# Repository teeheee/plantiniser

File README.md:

# Description

A watering system

# Usage Guide

# Platformio Commands

## Run unit tests

> pio test -e native

## Run hardware interface tests

> pio run -e hal_test -t upload

## RUN main program

> pio run -e main -t upload

## interface over usb

> pio run -e main -t monitor

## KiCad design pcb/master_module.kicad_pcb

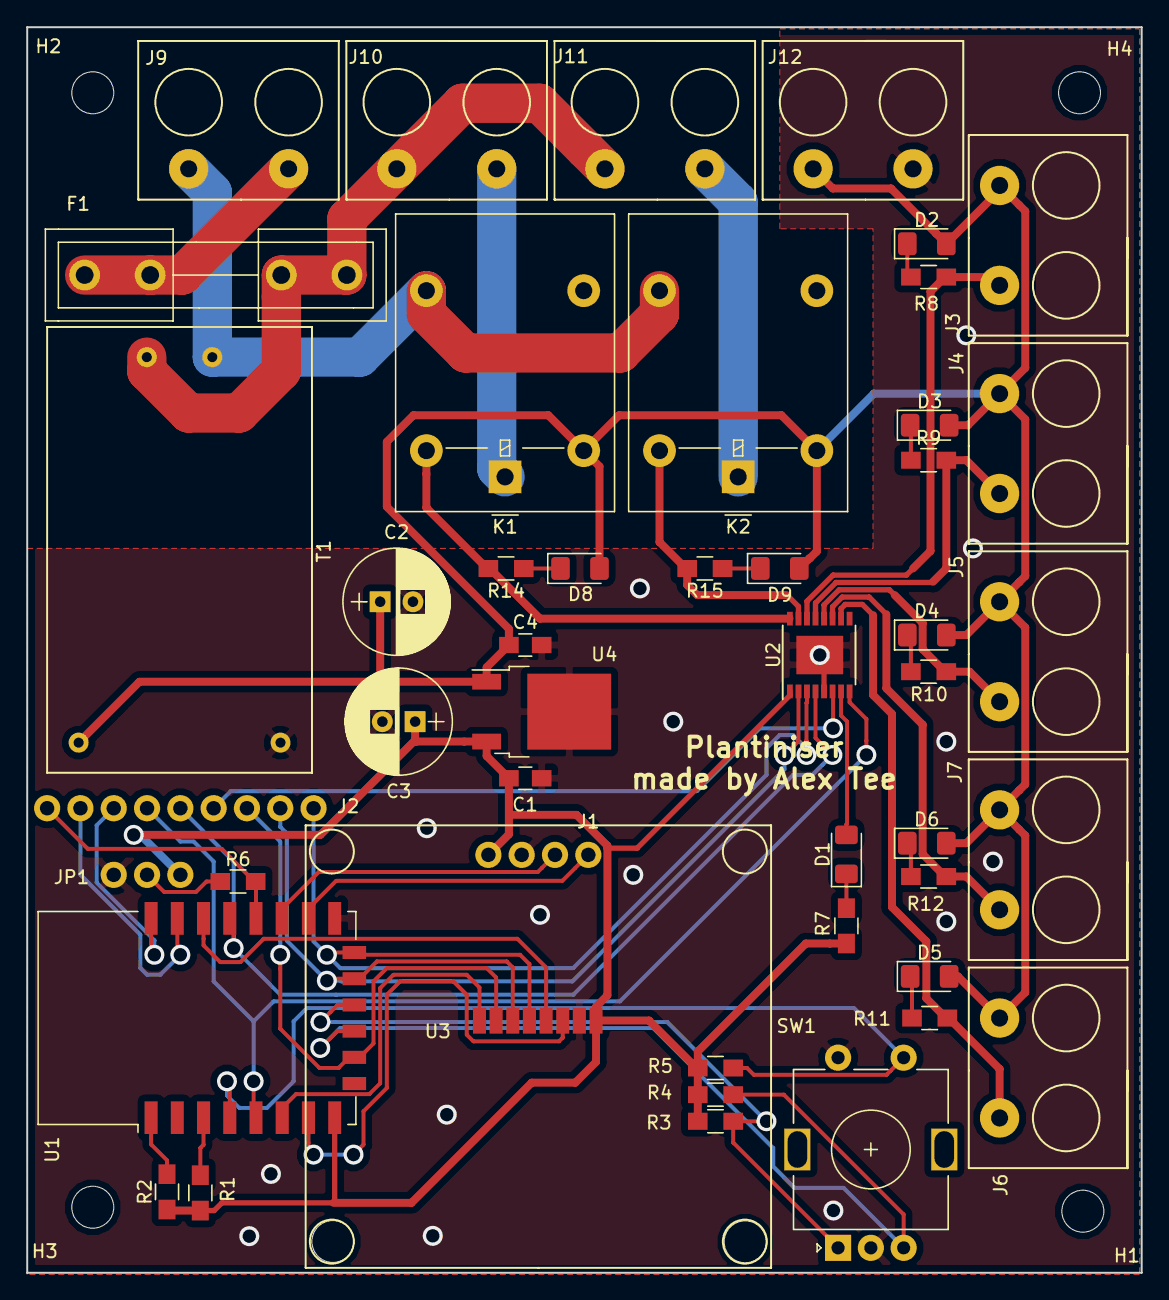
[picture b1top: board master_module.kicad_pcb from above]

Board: 2 copper layers, 85.0 x 95.0 mm, 51 parts (0 on the bottom side), 44 nets.

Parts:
C1, C4: 100nF; Kondensator_SMD_0805
C2, C3: 47uF; Kondensator_THT_8mm
D1, D2, D3, D4, D5, D6, D8, D9: LED; LED_SMD_1206
F1: Fuse; Sicherung_THT
H1, H2, H3, H4: MountingHole; MountingHole_3.2mm_M3_DIN965
J1: OLED; i2c_oled_1.3Zoll
J2: interface; CON_Stiftleiste_9x1
J3: 12V_OUT1; terminal_block_2pin
J4: 12V_OUT2; terminal_block_2pin
J5: 12V_OUT3; terminal_block_2pin
J6: 12V_OUT4; terminal_block_2pin
J7: 12V_OUT5; terminal_block_2pin
J9: 230V; terminal_block_2pin
J10: 230V_OUT1; terminal_block_2pin
J11: 230V_OUT2; terminal_block_2pin
J12: 12V_IN; terminal_block_2pin
JP1: Flash; CON_Stiftleiste_3x1
K1, K2: FINDER-40.11; Relay_SPDT_Omron-G5LE-1
R1, R2, R3, R4, R5, R6, R7: R; Wiederstand_SMD_0805
R8, R9, R10, R11, R12, R14, R15: 300; Wiederstand_SMD_0805
SW1: Rotary_Encoder_Switch; RotaryEncoder_Alps_EC11E-Switch_Vertical_H20mm
T1: HLK-PM12
U1: ESP-12E
U2: DRV8860_PWPR; TSSOP-16-1EP_4.4x5mm_P0.65mm
U3: NRF24L01; NRF24L01-SMD
U4: LF33_TO252; TO-252-2

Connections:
+3V3: C1.1, C3.1, J1.4, JP1.1, R1.1, R2.1, R3.1, R4.1, R5.1, R7.2, U1.8, U2.1, U3.2, U4.3
+12V: C2.1, C4.1, D2.2, D3.2, D4.2, D5.2, D6.2, D8.2, D9.2, J3.1, J4.1, J5.1, J6.1, J7.1, J12.1, K1.2, K2.2, T1.4, U4.1
/230V_A: F1.2, J9.2
/230V_B: F1.1, J10.1, J11.1, T1.2
/230V_C: J9.1, K1.4, K2.4, T1.1
/230V_E: J10.2, K1.1
/230V_F: J11.2, K2.1
/MISO: J2.7, U1.10, U3.7
/MOSI: J2.8, U1.13, U2.2, U3.6
/RE3: J3.2, R8.2, U2.14
/RE4: J4.2, R9.2, U2.13
/RE5: J5.2, R10.2, U2.12
/RE6: J7.2, R12.2, U2.11
/RE7: J6.2, R11.2, U2.10
/SCLK: J2.9, U1.14, U2.3, U3.5
A: R3.2, SW1.A, U1.12
B: R4.2, SW1.B, U1.11
C: R5.2, SW1.S1, U1.4
CE: U1.7, U3.3
CSN: U1.20, U3.4
DOUT: J2.6, U2.6
ENABLE: J2.4, U1.5, U2.8
GND: C1.2, C2.2, C3.2, C4.2, J1.3, J12.2, JP1.3, SW1.C, SW1.S2, T1.3, U1.15, U2.5, U2.17, U3.1, U4.2
GPIO0: J2.1, R6.2, U1.18
IRQ: U1.6, U3.8
LATCH: J2.5, U1.19, U2.4
unnamed: D1.1, R7.1
unnamed: D1.2, U2.7
unnamed: D2.1, R8.1
unnamed: D3.1, R9.1
unnamed: D4.1, R10.1
unnamed: D5.1, R11.1
unnamed: D6.1, R12.1
unnamed: D8.1, R14.1
unnamed: D9.1, R15.1
unnamed: JP1.2, R6.1
unnamed: R1.2, U1.3
unnamed: R2.2, U1.1
RE1: K1.5, R14.2, U2.16
RE2: K2.5, R15.2, U2.15
RX: J2.2, U1.21
SCL: J1.2, U1.17
SDA: J1.1, U1.16
TX: J2.3, U1.22

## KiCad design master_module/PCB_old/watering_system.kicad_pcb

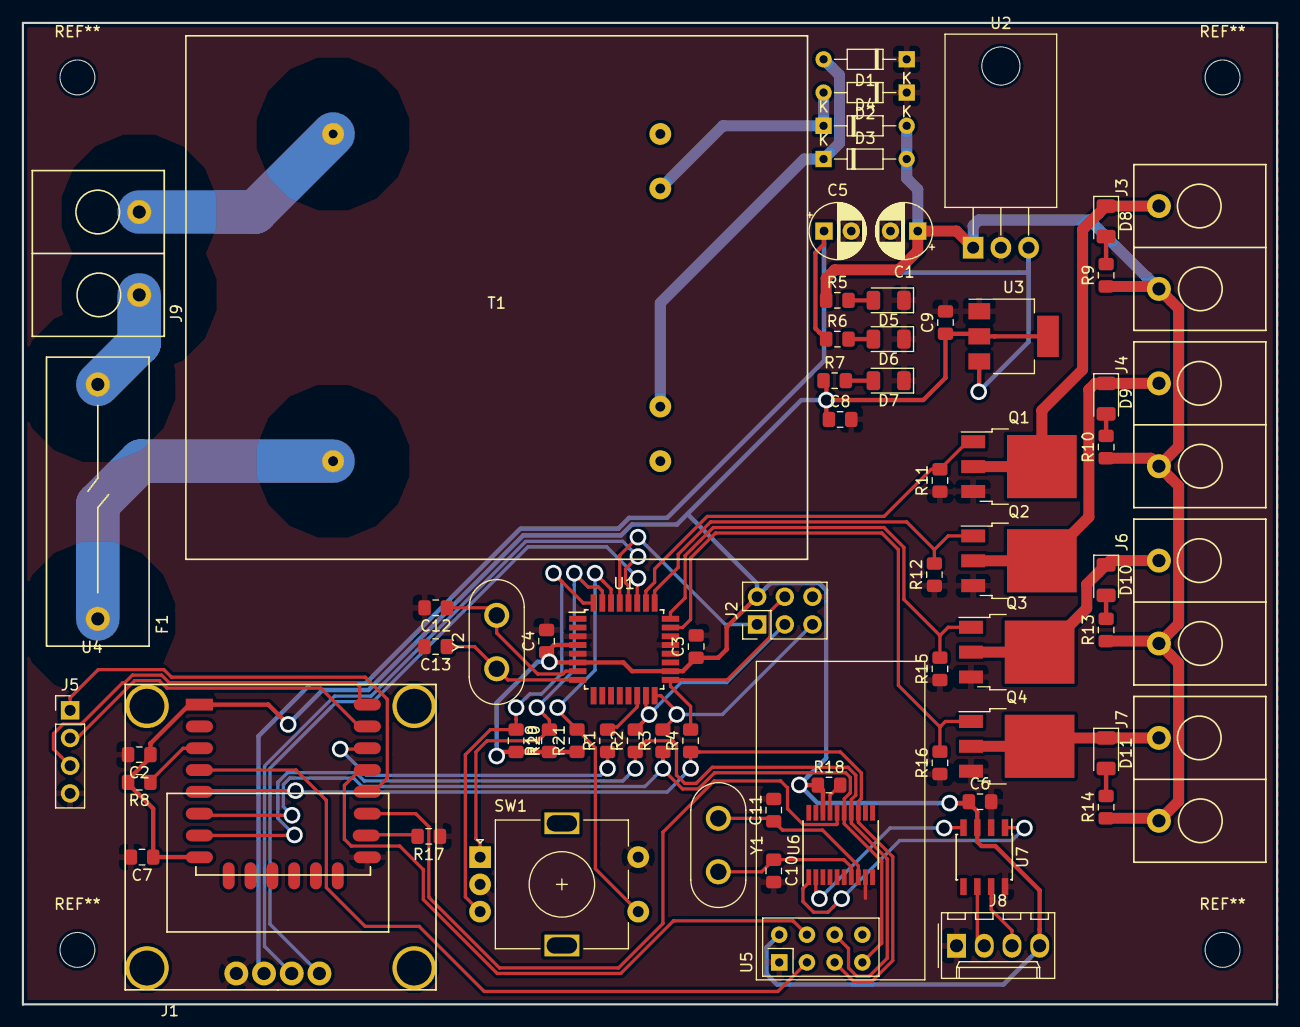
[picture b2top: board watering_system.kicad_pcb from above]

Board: 2 copper layers, 115.0 x 90.0 mm, 70 parts (0 on the bottom side), 55 nets.

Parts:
C1, C5: 47u; CP_Radial_D5.0mm_P2.50mm
C2, C3, C4, C6, C7, C8, C9: 100n; C_0805_2012Metric_Pad1.15x1.40mm_HandSolder
C10, C11, C12, C13: 22p; C_0805_2012Metric_Pad1.15x1.40mm_HandSolder
D1, D2, D3, D4: DIODE; D_DO-34_SOD68_P7.62mm_Horizontal
D5, D6, D7, D8, D9, D10, D11: LED; LED_1206_3216Metric
F1: Fuse; fuse
J1: Oled; i2c_oled_0_95_inch
J2: AVR-ISP-6; PinHeader_2x03_P2.54mm_Vertical
J3: A1_CON; HP_Connector_2pin
J4: A2_CON; HP_Connector_2pin
J5: esp_serial; PinHeader_1x04_P2.54mm_Vertical
J6: A3_CON; HP_Connector_2pin
J7: A4_CON; HP_Connector_2pin
J8: CAN; Molex_KK-254_AE-6410-04A_1x04_P2.54mm_Vertical
J9: MAINS; HP_Connector_2pin
Q1, Q2, Q3, Q4: IRFR1205; TO-252-3_TabPin2
R1, R2, R3, R4, R5, R8, R9, R10, R11, R12, R13, R14, R15, R16, R17, R18, R19, R20, R21: 1k; R_0805_2012Metric_Pad1.15x1.40mm_HandSolder
R6, R7: 330; R_0805_2012Metric_Pad1.15x1.40mm_HandSolder
SW1: Rotary_Encoder_Switch; RotaryEncoder_Alps_EC11E-Switch_Vertical_H20mm
T1: Transformer_1P_1S; PrintTrafo_16VA
U1: ATmega8-16AU; TQFP-32_7x7mm_P0.8mm
U2: L7805; TO-220-3_Horizontal_TabDown
U3: LD1117S33TR_SOT223; SOT-223-3_TabPin2
U4: ESP-12; ESP-12E
U5: NRF24L01_Breakout; nRF24L01_Breakout
U6: MCP2515-EST; TSSOP-20_4.4x6.5mm_P0.65mm
U7: TJA1051T; SOIC-8_3.9x4.9mm_P1.27mm
Y1, Y2: 16Mhz; Crystal_HC50_Vertical

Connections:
+3V3: C2.1, C3.1, C4.1, C6.1, C7.1, C8.1, C9.1, J2.2, J8.4, R7.1, R8.2, R18.1, R19.1, R20.2, R21.1, U1.4, U1.6, U1.18, U3.2, U4.1, U4.8, U5.2, U6.18, U7.3
+5V: C5.1, J1.2, R6.1, U2.3, U3.3
+12V: C1.1, D3.2, D4.2, J3.2, J4.2, J6.2, J7.2, R5.1, R9.1, R10.1, R13.1, R14.1, U2.1
/CE_NRF: U4.4, U5.3
/MISO: R3.1, U4.6, U5.7, U6.15
/MOSI: R2.1, U4.7, U5.6, U6.14
/SCK: R4.1, U4.5, U5.5, U6.13
/SS_AVR: R1.1, U4.14
/SS_CAN: U4.11, U6.16
/SS_NRF: U4.13, U5.4
A1: Q1.1, R11.2, U1.26
A2: Q2.1, R12.2, U1.25
A3: Q3.1, R15.2, U1.24
A4: Q4.1, R16.2, U1.23
EA: R19.2, SW1.A, U1.31
EB: R20.1, SW1.B, U1.32
ES: R21.2, SW1.S1, U1.30
GND: C1.2, C2.2, C3.2, C4.2, C5.2, C6.2, C7.2, C8.2, C9.2, C10.2, C11.2, C12.2, C13.2, D1.1, D2.1, D5.1, D6.1, D7.1, J1.1, J2.6, J5.4, J8.1, Q1.3, Q2.3, Q3.3, Q4.3, R11.1, R12.1, R15.1, R16.1, R17.1, SW1.C, SW1.S2, U1.3, U1.5, U1.21, U2.2, U3.1, U4.9, U5.1, U6.9, U7.2, U7.8
unnamed: C10.1, U6.7, Y1.2
unnamed: C11.1, U6.8, Y1.1
unnamed: C12.1, U1.7, Y2.2
unnamed: C13.1, U1.8, Y2.1
unnamed: D1.2, D3.1, T1.3
unnamed: D2.2, D4.1, T1.4
unnamed: D5.2, R5.2
unnamed: D6.2, R6.2
unnamed: D7.2, R7.2
unnamed: D8.1, J3.1, Q1.2
unnamed: D8.2, R9.2
unnamed: D9.1, J4.1, Q2.2
unnamed: D9.2, R10.2
unnamed: D10.1, J6.1, Q3.2
unnamed: D10.2, R13.2
unnamed: D11.1, J7.1, Q4.2
unnamed: D11.2, R14.2
unnamed: F1.1, T1.1
unnamed: F1.2, J9.1
unnamed: J2.1, U1.29
unnamed: J2.3, R2.2, U1.15
unnamed: J2.4, R4.2, U1.17
unnamed: J2.5, R3.2, U1.16
unnamed: J5.1, U4.12
unnamed: J5.2, U4.15
unnamed: J5.3, U4.16
unnamed: J8.2, U7.6
unnamed: J8.3, U7.7
unnamed: J9.2, T1.2
unnamed: R1.2, U1.14
unnamed: R8.1, U4.3
unnamed: R17.2, U4.10
unnamed: R18.2, U6.17
unnamed: U6.1, U7.1
unnamed: U6.2, U7.4
SCL: J1.3, U1.28
SDA: J1.4, U1.27

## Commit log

2019-06-05 wire shuffling
2019-07-26 first pcb version
2019-07-26 final version pcb
2020-03-17 hardware abstraction almost finished
2020-03-21 added box
2020-03-22 started unit testing config tool
2020-04-12 google test working
2020-04-12 cleanup
2020-04-12 all tests pass
2020-04-13 working config
2020-06-10 update firmware
2020-09-16 some fixes
2020-09-16 restructure
2020-09-16 added workflow
2020-09-16 added publishing
2020-09-16 made action trigger on release
2021-02-26 added DS1307 RTC
2021-02-26 added time configuration
2021-02-26 added top box stl
2021-02-26 started moisture sensor
2021-02-27 new housing design
2021-02-28 removed itoa dependencie in config items
2021-02-28 added app class
2021-02-28 added ota with http server
2021-02-28 cleanup ini file
2021-02-28 fixed hal test
2021-03-03 refactor major parts of the codebase
2021-03-05 added jenkins pipeline
2021-03-05 upadte jenkinsfile
2021-03-05 update jenkins file
2021-03-07 Create Dockerfile
2021-03-07 Update Dockerfile
2021-03-08 Update Jenkinsfile
2021-03-09 added test to pipline
2021-03-09 cleanup include files
2021-03-09 cleanup build
2021-03-09 added trim to config
2021-03-09 fixed unit test
2021-03-09 added check always for update
2021-03-09 disable debug in ota driver
2021-03-11 updated schematic
2021-03-11 added mock classes and nrf24 support
2021-03-12 added temperature node
2021-03-12 bugfixes nrf24 to mqtt passthrough
2021-03-12 fixes ota update
2021-03-21 bugfix for mqtt connection lost issue
2021-03-23 added temperatur dht22 node
2021-03-23 added check for rtc
2021-03-23 fixed unit tests
2021-03-24 implemented new encode
